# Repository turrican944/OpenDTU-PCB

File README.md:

# OpenDTU-PCB      
   
Eine Leiterplatte für OpenDTU oder Ahoy mit Oled Display.
Gehäuse Gainta G203CMF 115 x 65 x 40

Neue PCB Version jetzt mit CMT2300a und NRF24L01+
Es kann ein 1.3" Oled oder 0.9" I2C Oled verbaut werden. Die Polung der Spannungsversorgung ist über Jumper einstellbar. NRF24L01+ als Standart mit PCB Antenne oder auch als Version mit externer Antenne.
Es kann ein Wemos D1 mini oder ein Wemos D1 ESP32 verbaut werden. Für OpenDTU wird der Wemos D1 ESP32 benötigt.

Das GPIO Pinning ist das Standartpinning vom AhoyDTU. OpenDTU muss entsprechend auf angepasst werden (Deviceprofil.json für OpenDTU mit und ohne Display).
GPIO Pins OpenDTU: <br>
NRF: <br>
IO17 IRQ <br>
IO16 CE <br>
IO05 CS <br>
IO23 MOSI <br>
IO19 MISO <br>
IO18 SCK <br>
Display: <br>
IO22 SCL <br>
IO21 SDA <br>
CMT2300a: <br>
IO14 SDIO <br>
IO12 SCLK <br>
IO27 CSN <br>
IO26 FCSB <br>
IO04 GPIO2 <br>
IO13 GPIO3 <br>
LED: <br>
IO32 LED0 <br>
IO33 LED1 <br>

Die Pins legt man am besten schon in der Platformio.ini fest. Der ESP D1 Mini ist in der Platformio.ini schon enthalten allerdings sind dort IO16 und IO17 vertauscht. Flasht man nun den ESP32 wenn der schon auf de Platine ist, gibts beim Starten immer einen Interrupt vom Funkmodul (Pinning stimmt ja nicht) und ggf. kommt man dann nicht auf das WebIF. Also am besten die Pins des Funkmodul schon vorher ändern oder ESP32 erst flashen, devices config nachladen und ESP32 auf der Platine verbauen.

Bauteile: <br>
Wemos D1 ESP32 (für OpenDTU oder Ahoy) https://www.az-delivery.de/collections/esp32/products/esp32-d1-mini <br>
NRF24L01+ Funkmodul <br>
470uF Kondensator (es müssen wohl nicht umbedingt 470uF sein, weniger geht wohl auch ggf das nehmen was in der Bastelkiste grade ist)<br>
Minicombicon wenn die Stromversorgung nicht über den USB Port erfolgen soll. https://www.reichelt.de/stiftleiste-2-pol-rm-3-81-mm-0--ctb932ve-2-p292580.html?&nbc=1&trstct=lsbght_sldr::292630 <br>
Gainta G203CMF 115 x 65 x 40 Gehäuse https://www.conrad.de/de/p/gainta-g203cmf-universal-gehaeuse-115-x-65-x-40-polycarbonat-hellgrau-klar-1-st-2356897.html <br>
Ahoy mit einem ESP32 habe ich auf der aktuelle Platine nicht getestet.

Olimex ESP32 Poe
Adapterplatine CMT2300a auf Olimex poe Board

Die Gerberdaten der Olimex Platine sind auch Panel 2x4 vorhanden.

Gehäuse für den Olimex ISO
https://www.thingiverse.com/thing:6489072 <br>
Gehäuse Olimex https://www.thingiverse.com/thing:4860626 (das ist das auf dem Bild)

Dieses Werk ist lizenziert unter einer [Creative Commons Namensnennung - Nicht-kommerziell - Weitergabe unter gleichen Bedingungen 4.0 International Lizenz](http://creativecommons.org/licenses/by-nc-sa/4.0/).

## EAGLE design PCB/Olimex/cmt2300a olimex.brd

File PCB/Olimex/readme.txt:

olimex_muster.zip enthält alle Gerber und Excellon Daten zum Fertigen z.b. bei JLCPCB 8 Muster sind auf einer Leiterplatte.
Wenn man die Standartmenge mit 5 Leiterplatten bestellt bekommt man also 40 Leiterplatten 

olimex.zip enthält die Gerber, Excellon und Eagle Daten für eine Leiterplatte.

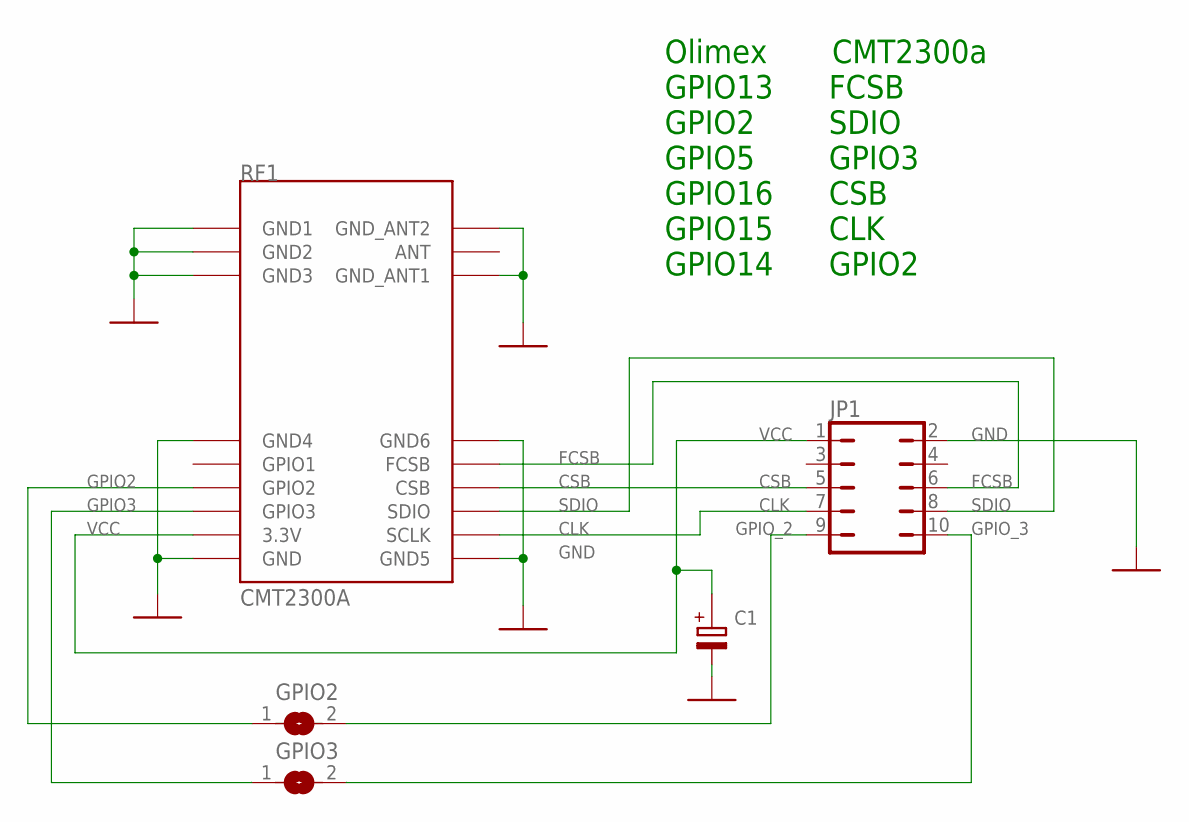
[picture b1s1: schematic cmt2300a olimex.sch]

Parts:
C1: S470µ/16; EB10D
GPIO2, GPIO3: SJ
JP1: JP5Q_OT
RF1: CMT2300A

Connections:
CLK: JP1.7, RF1.SCLK
CSB: JP1.5, RF1.CSB
FCSB: JP1.6, RF1.FCSB
GND: C1.-, JP1.2, RF1.GND, RF1.GND1, RF1.GND2, RF1.GND3, RF1.GND4, RF1.GND5, RF1.GND6, RF1.GND_ANT1, RF1.GND_ANT2
GPIO2: GPIO2.1, RF1.GPIO2
GPIO3: GPIO3.1, RF1.GPIO3
GPIO_2: GPIO2.2, JP1.9
GPIO_3: GPIO3.2, JP1.10
SDIO: JP1.8, RF1.SDIO
VCC: C1.+, JP1.1, RF1.3.3V

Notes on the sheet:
Olimex CMT2300a GPIO13 FCSB GPIO2 SDIO GPIO5 GPIO3 GPIO16 CSB GPIO15 CLK GPIO14 GPIO2

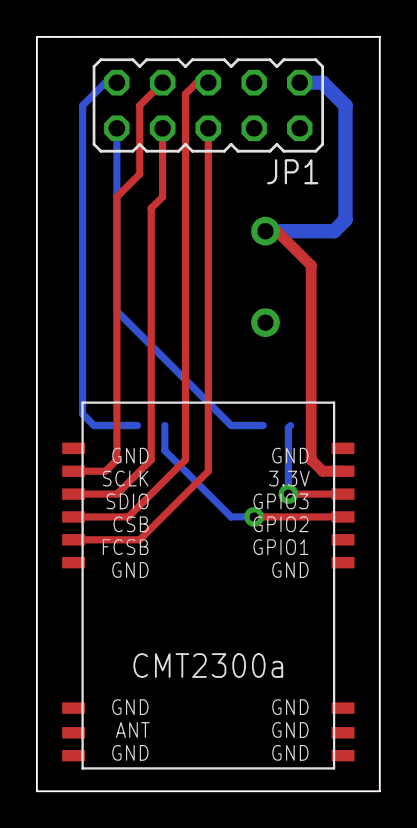
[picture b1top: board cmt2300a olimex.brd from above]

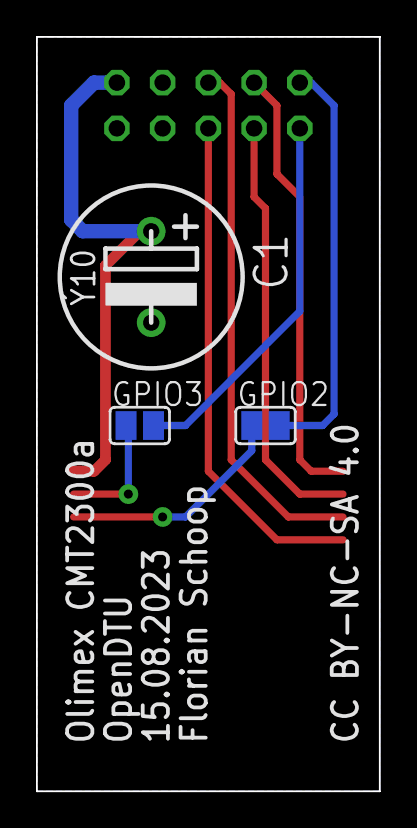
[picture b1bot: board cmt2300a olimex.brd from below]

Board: 2 copper layers, 19.1 x 41.9 mm, 5 parts (3 on the bottom side), 10 nets.

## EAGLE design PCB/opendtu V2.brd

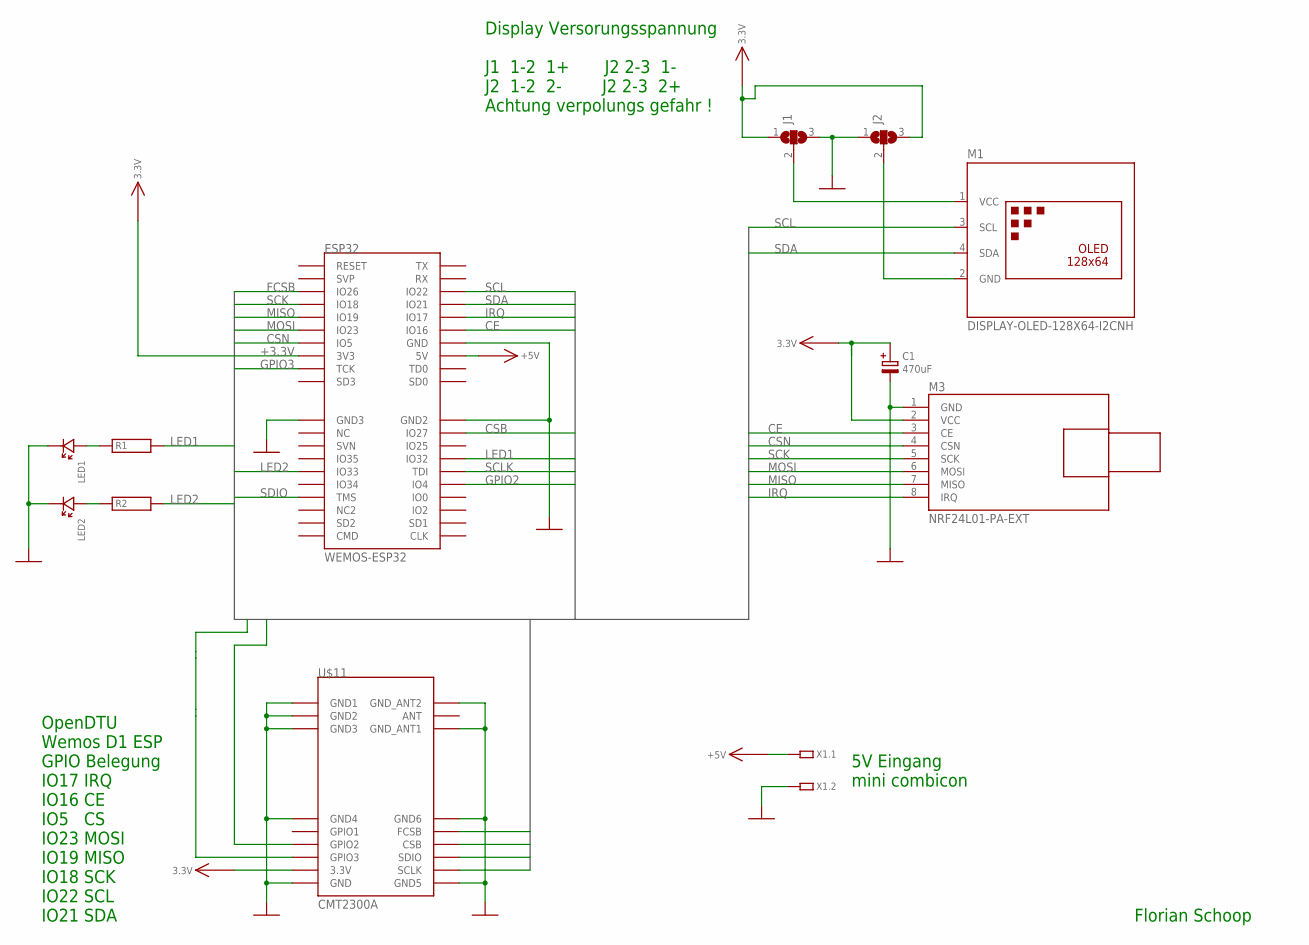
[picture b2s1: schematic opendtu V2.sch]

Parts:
C1: 470uF; EB10D
ESP32: WEMOS-ESP32
J1, J2: SJ2W; SJ_2
LED1, LED2: LED3MM
M1: DISPLAY-OLED-128X64-I2CNH; DISPLAY-OLED-128X64-I2C_NH
M3: NRF24L01-PA-EXT
R1, R2: WIDERSAND; 1/8W
U$11: CMT2300A
X1: MCV1,5/2G; MCV1,5/2

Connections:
+3.3V: C1.+, ESP32.3V3, J1.1, J2.3, M3.2 (VCC), U$11.3.3V
+5V: ESP32.VCC (5V), X1.1
CE: ESP32.IO16, M3.3 (CE)
CSB: ESP32.IO27, U$11.CSB
CSN: ESP32.IO5, M3.4 (CSN)
FCSB: ESP32.IO26, U$11.FCSB
GND: C1.-, ESP32.GND, ESP32.GND2, ESP32.GND3, J1.3, J2.1, LED1.K (KAT), LED2.K (KAT), M3.1 (GND), U$11.GND, U$11.GND1, U$11.GND2, U$11.GND3, U$11.GND4, U$11.GND5, U$11.GND6, U$11.GND_ANT1, U$11.GND_ANT2, X1.2
GPIO2: ESP32.IO4, U$11.GPIO2
GPIO3: ESP32.TCK, U$11.GPIO3
IRQ: ESP32.IO17, M3.8 (IRQ)
LED1: ESP32.IO32, R1.2
LED2: ESP32.IO33, R2.2
MISO: ESP32.IO19, M3.7 (MISO)
MOSI: ESP32.IO23, M3.6 (MOSI)
unnamed: J2.2, M1.2 (GND)
unnamed: J1.2, M1.1 (VCC)
unnamed: LED2.A (ANO), R2.1
unnamed: LED1.A (ANO), R1.1
SCK: ESP32.IO18, M3.5 (SCK)
SCL: ESP32.IO22, M1.3 (SCL)
SCLK: ESP32.TDI, U$11.SCLK
SDA: ESP32.IO21, M1.4 (SDA)
SDIO: ESP32.TMS, U$11.SDIO

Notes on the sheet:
Display Versorungsspannung J1 1-2 1+ J2 2-3 1- J2 1-2 2- J2 2-3 2+ Achtung verpolungs gefahr !
OpenDTU Wemos D1 ESP GPIO Belegung IO17 IRQ IO16 CE IO5 CS IO23 MOSI IO19 MISO IO18 SCK IO22 SCL IO21 SDA
Florian Schoop
5V Eingang mini combicon

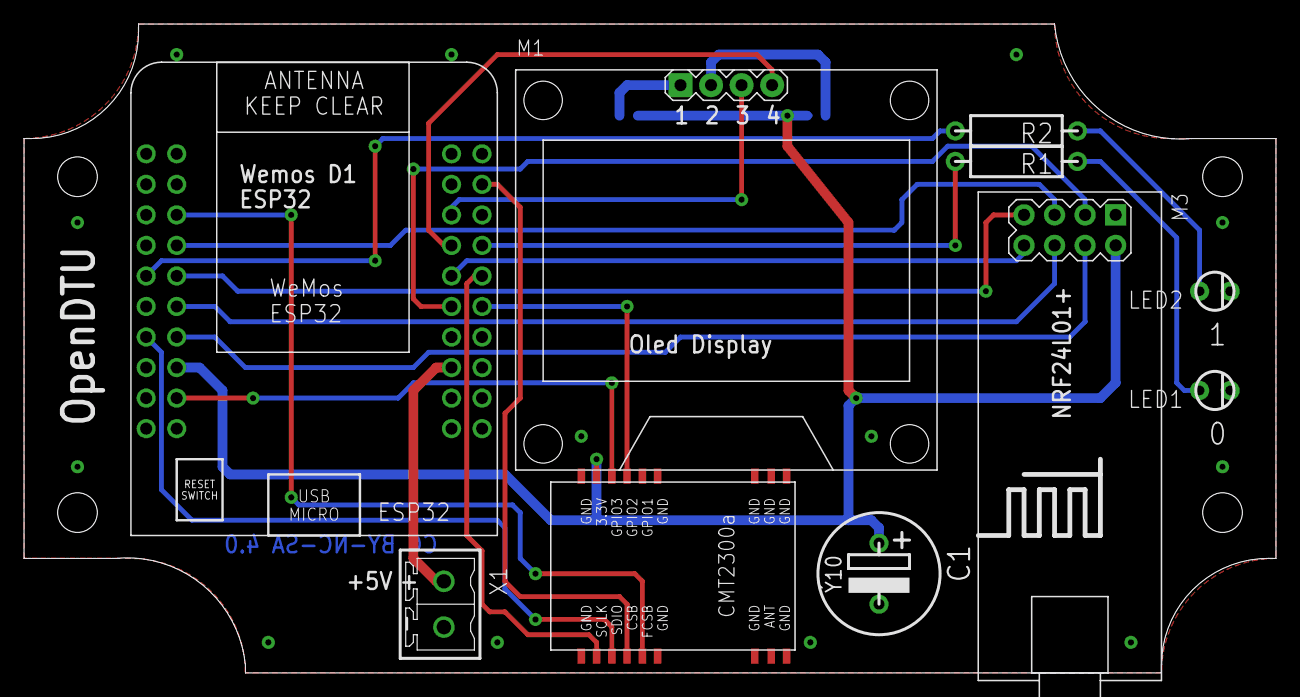
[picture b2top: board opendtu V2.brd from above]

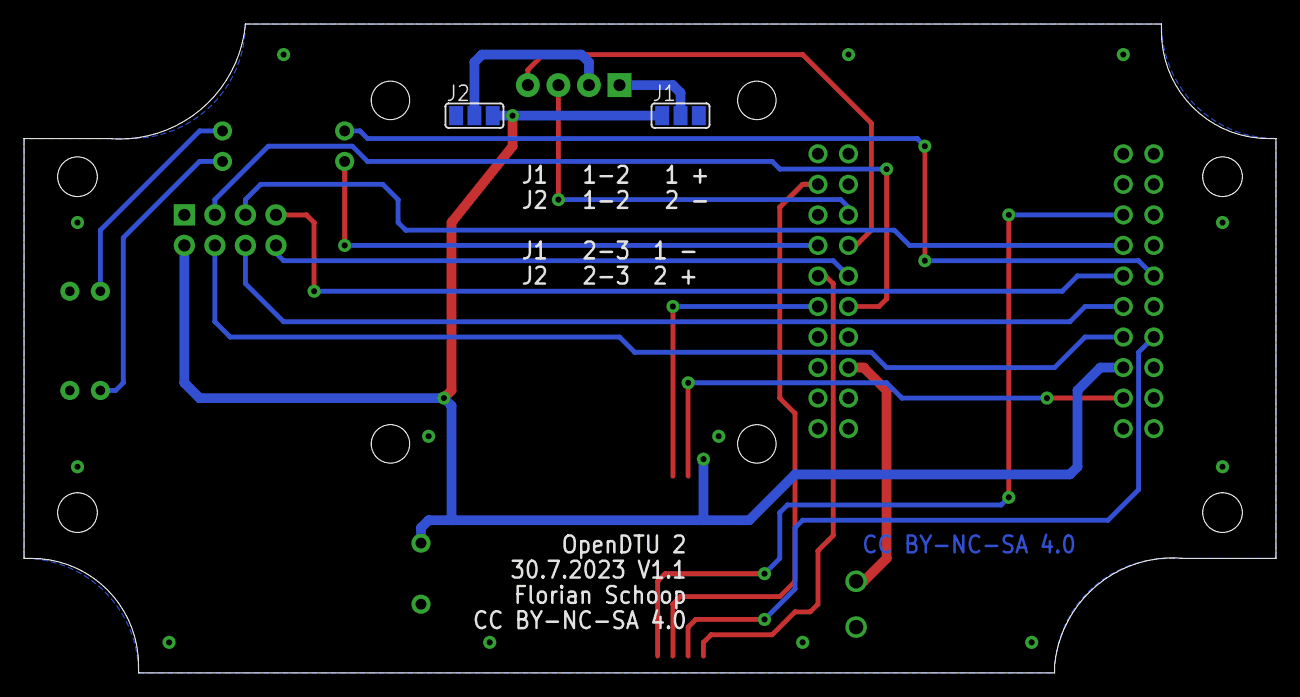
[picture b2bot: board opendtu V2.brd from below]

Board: 2 copper layers, 104.1 x 54.0 mm, 12 parts (2 on the bottom side), 23 nets.

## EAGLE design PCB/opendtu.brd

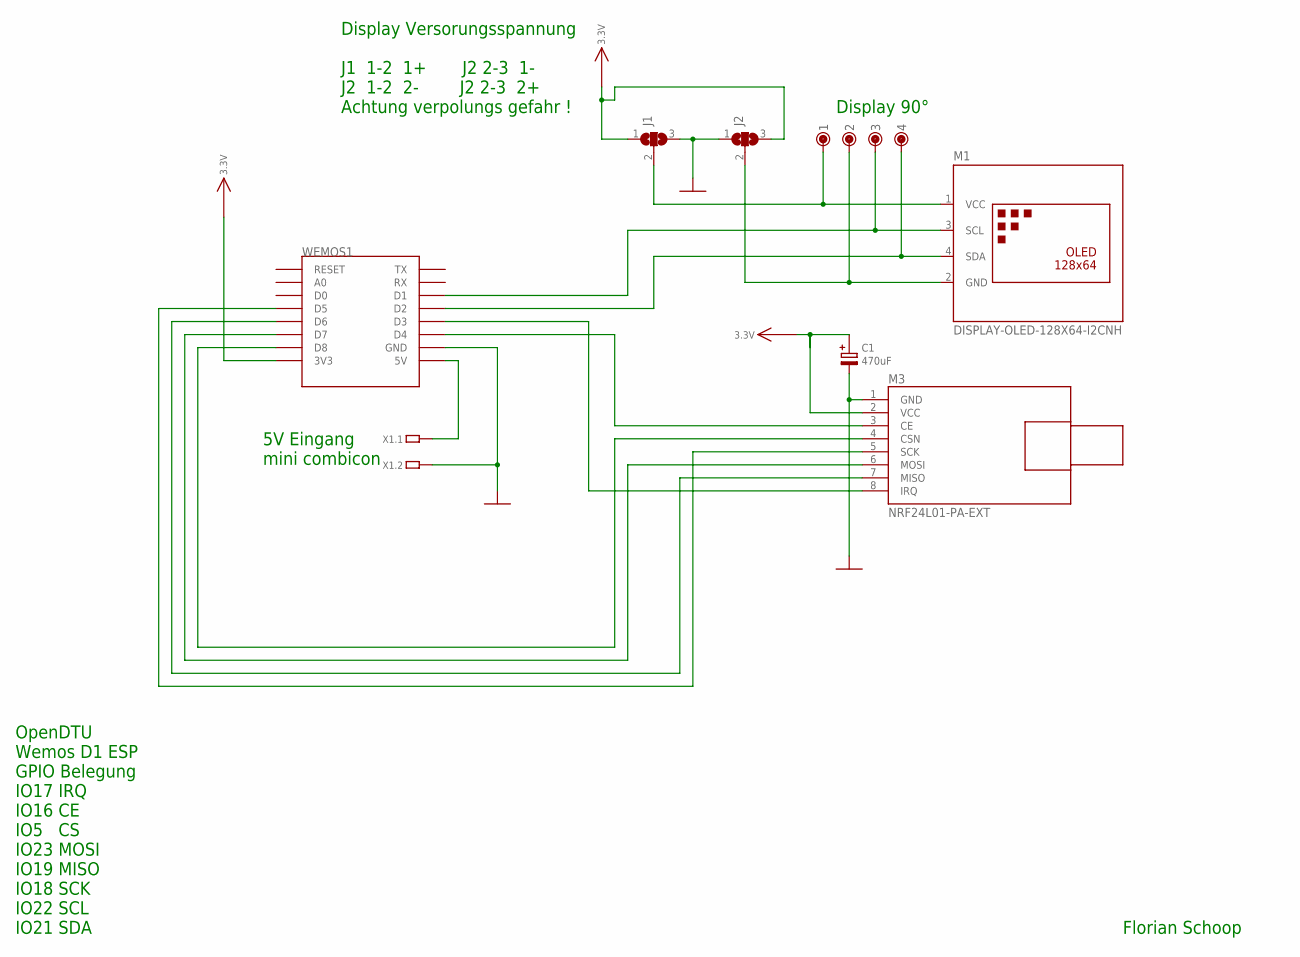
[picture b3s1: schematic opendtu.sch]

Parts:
1, 2, 3, 4: PINGERAD
C1: 470uF; EB10D
J1, J2: SJ2W; SJ_2
M1: DISPLAY-OLED-128X64-I2CNH; DISPLAY-OLED-128X64-I2C_NH
M3: NRF24L01-PA-EXT
WEMOS1: WEMOS-D1-MINI
X1: MCV1,5/2G; MCV1,5/2

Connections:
+3.3V: C1.+, J1.1, J2.3, M3.2 (VCC), WEMOS1.3V3
GND: C1.-, J1.3, J2.1, M3.1 (GND), WEMOS1.GND, X1.2
unnamed: 4.1, M1.4 (SDA), WEMOS1.D2
unnamed: 3.1, M1.3 (SCL), WEMOS1.D1
unnamed: 2.1, J2.2, M1.2 (GND)
unnamed: 1.1, J1.2, M1.1 (VCC)
unnamed: M3.3 (CE), WEMOS1.D4
unnamed: M3.4 (CSN), WEMOS1.D8
unnamed: M3.6 (MOSI), WEMOS1.D7
unnamed: M3.7 (MISO), WEMOS1.D6
unnamed: M3.5 (SCK), WEMOS1.D5
unnamed: M3.8 (IRQ), WEMOS1.D3
unnamed: WEMOS1.5V, X1.1

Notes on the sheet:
Display Versorungsspannung J1 1-2 1+ J2 2-3 1- J2 1-2 2- J2 2-3 2+ Achtung verpolungs gefahr !
Display 90°
OpenDTU Wemos D1 ESP GPIO Belegung IO17 IRQ IO16 CE IO5 CS IO23 MOSI IO19 MISO IO18 SCK IO22 SCL IO21 SDA
Florian Schoop
5V Eingang mini combicon

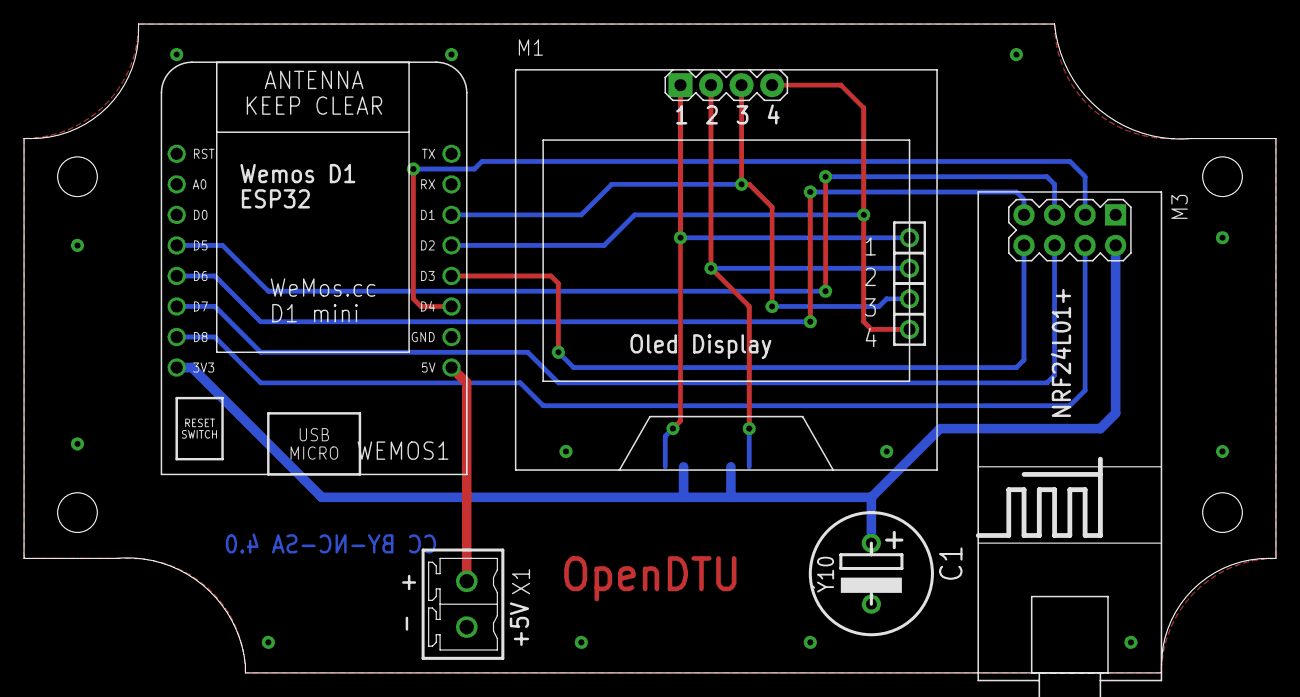
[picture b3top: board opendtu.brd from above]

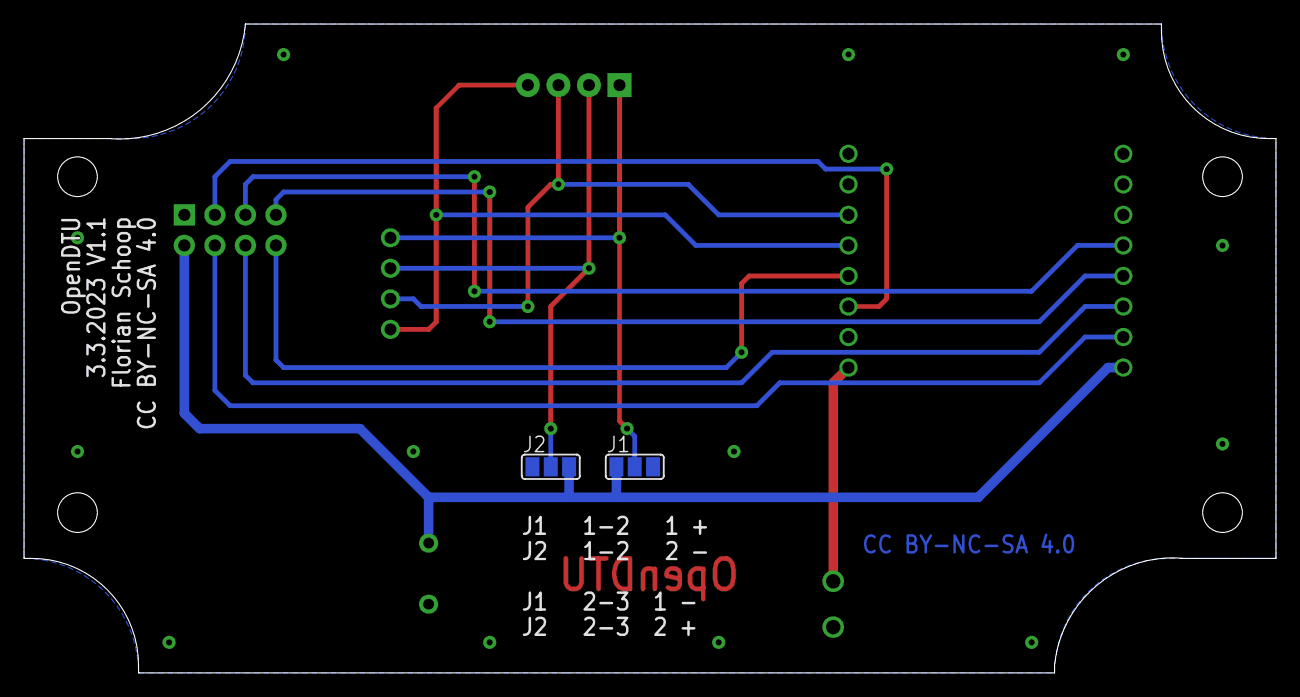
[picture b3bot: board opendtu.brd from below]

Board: 2 copper layers, 104.1 x 54.0 mm, 11 parts (2 on the bottom side), 13 nets.

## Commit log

2023-02-24 erste upload
    erster Upload
2023-02-24 Create opendtu.sch
    Schaltplan
2023-02-24 Schematic
    Schaltplan änderungen
2023-02-24 Board
    Passlöcher vom Board entfernt. Werden zur Produktion nicht benötig. Passlöcher nur fürs Sieb & Meyer Fräsefile benötig. (für das Bohrmuster).
2023-02-24 PCB Bilder
    Bilder
2023-02-28 Text Display
    Display Text geändert, damit der auch unter den PINs ist.
2023-03-01 Eagle backup
    Eagle Backup Dateien nicht synchronisieren
2023-03-02 masse
    Masse Via hinzugefügt
2023-03-02 Create OpenDTU-V1.zip
    Zip Datei mit der ersten Version.
2023-03-03 Gerber V1.1
    V1.1 vom Gerber
2023-03-03 V1.1
    V1.1 hinzugefügt
2023-03-04 V1.1
    Text nochmal etwas verschoben. PDF vom Schaltplan hinzugefügt.
2023-03-04 Bild
    Bild hinzugefügt
2023-03-05 add Deviceprofil.json
    Deviceprofil für ESP32, für OpenDTU. Nach dem Flashen vom OpenDTU kann diese Datei über das Webif geladen werden und damit die GPIO Pins passend auszuwählen. (kann natürlich auch schon beim Compilier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
2023-03-05 remove gitignor.bak
2023-03-12 add platformio_override.ini
    Platformio_overide.ini passend für Wemos D1 ESP32 mit Display
2023-03-16 V1 entfernt
    V1 entfernt, V1.1 ist ok
2023-06-12 Update Device Profil D1 ESP32.json
    update Device profil
2023-07-30 add CMT2300a
    V2 mit CMT2300a (ungetestet !!)
2023-07-30 plus war im weg
    plus war im weg
2023-07-31 Bild
    Bild OpenDTU V2
2023-08-03 Via geändert
2023-08-15 Schaltplan PDF
2023-08-28 add olimex
2023-08-28 olimex
2023-08-28 Update README.md
    add olimex Board
2023-10-06 Update Device Profil D1 ESP32.json
    Add Olimex POE CMT2300a
2023-11-03 Update opendtu V2.pdf
    nur noch eine Seite
2023-11-03 Update cmt2300a olimex.pdf
    pin config hinzugefügt
2023-11-03 Update Device Profil D1 ESP32.json
    Text änderungen
2024-01-07 Update Device Profil D1 ESP32.json
    Without these additional lines, which deactivate the pins for nrf24, Ethernet did not work. The problem seemed to come from the fact that pins are defined for the nrf24 in the standard configuration,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
    After inserting these lines, Ethernet worked without any problems.
2024-02-23 Update README.md
    neue Leiterplatten Bilder mit CMT2300a und NRF
2024-02-23 move old files
    move old PCB to old folder, remove Eagle undo files
2024-02-23 Update README.md
    add link Olimex Case
2024-02-23 add readme
    add readme.txt olimex
2024-02-23 Update README.md
    olimex iso
2024-02-23 Update README.md
    olimex case link
2024-03-08 Bezeichnung korrigiert
    Beschreibung J1 und J2 im Schaltplan war falsch.
2024-04-18 Update Device Profil D1 ESP32.json
    Add Olimex PEO with NRF24L01 and Display
2024-07-30 ESP32 lange version
    ESP32 lang hinzugefügt
2024-08-06 Update README.md
    Display 90 grad entfernt.

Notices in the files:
PCB/Olimex/cmt2300a olimex.brd:
CC BY-NC-SA 4.0
README.md:
License: CC BY-NC-SA 4.0
Creative Commons Lizenzvertrag
